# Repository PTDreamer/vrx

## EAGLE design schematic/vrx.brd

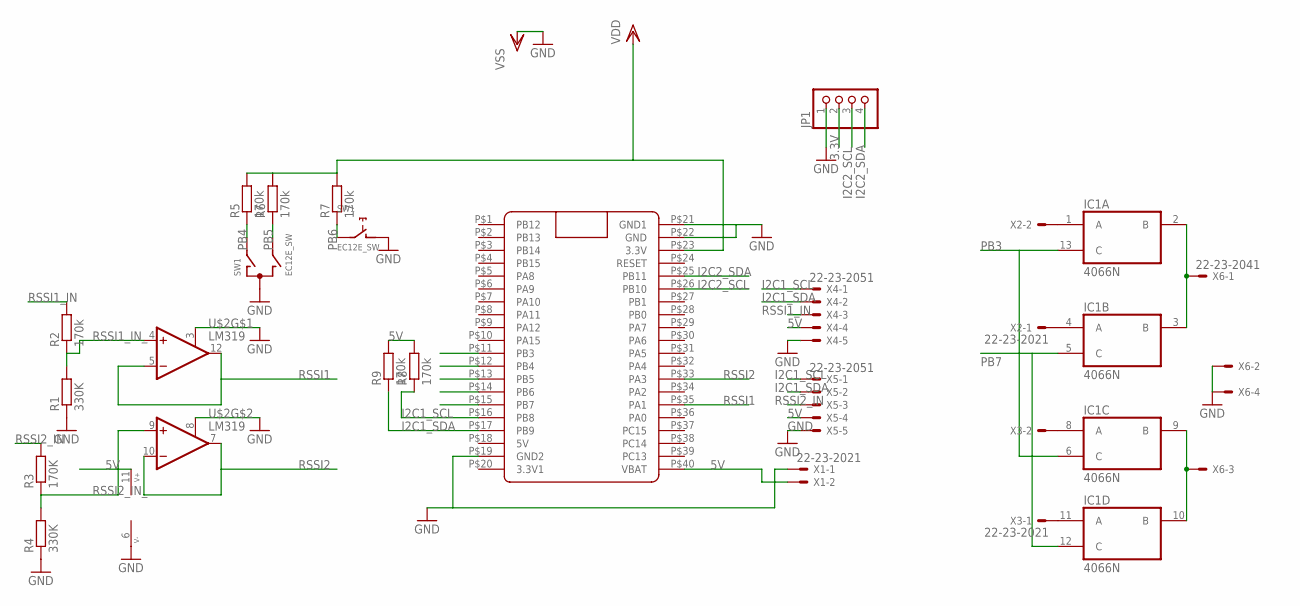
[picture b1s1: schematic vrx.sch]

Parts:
IC1: 4066N; DIL14
JP1: PINHD-1X4; 1X04
R1, R4: 330K; 0204/7
R2, R5, R6, R7, R8, R9: 170k; 0204/7
R3: 170K; 0204/7
SW1: EC12E_SW; ALPS_EC12E_SW
U$1: BLUE_PILLADVANCED; BLUE_PILL_ADV
U$2: LM319; DIL14
X1, X2, X3: 22-23-2021
X4, X5: 22-23-2051
X6: 22-23-2041

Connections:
3.3V: JP1.2
5V: R8.2, R9.2, U$1.P$40 (VBAT), U$2.11 (V+), X1.2, X4.4, X5.4
GND: IC1.7 (VSS), JP1.1, R1.1, R4.1, SW1.C, SW1.D (1), U$1.P$19 (GND2), U$1.P$21 (GND1), U$1.P$22 (GND), U$2.3 (SHDN), U$2.6 (V-), U$2.8 (SHDN), X1.1, X4.5, X5.5, X6.2, X6.4
I2C1_SCL: R8.1, U$1.P$16 (PB8), X4.1, X5.1
I2C1_SDA: R9.1, U$1.P$17 (PB9), X4.2, X5.2
I2C2_SCL: JP1.3, U$1.P$26 (PB10)
I2C2_SDA: JP1.4, U$1.P$25 (PB11)
unnamed: IC1.2 (B), IC1.3 (B), X6.1
unnamed: IC1.9 (B), IC1.10 (B), X6.3
unnamed: IC1.1 (A), X2.2
unnamed: IC1.4 (A), X2.1
unnamed: IC1.8 (A), X3.2
unnamed: IC1.11 (A), X3.1
PB3: IC1.6 (C), IC1.13 (C), U$1.P$11 (PB3)
PB4: R5.1, SW1.A, U$1.P$12 (PB4)
PB5: R6.1, SW1.B, U$1.P$13 (PB5)
PB6: R7.1, SW1.E (2), U$1.P$14 (PB6)
PB7: IC1.5 (C), IC1.12 (C), U$1.P$15 (PB7)
RSSI1: U$1.P$35 (PA1), U$2.5 (-IN), U$2.12 (OUT)
RSSI1_IN: R2.2, X4.3
RSSI1_IN_: R1.2, R2.1, U$2.4 (+IN)
RSSI2: U$1.P$33 (PA3), U$2.7 (OUT), U$2.10 (-IN)
RSSI2_IN: R3.2, X5.3
RSSI2_IN_: R3.1, R4.2, U$2.9 (+IN)
VDD: IC1.14 (VDD), R5.2, R6.2, R7.2, U$1.P$23 (3.3V)

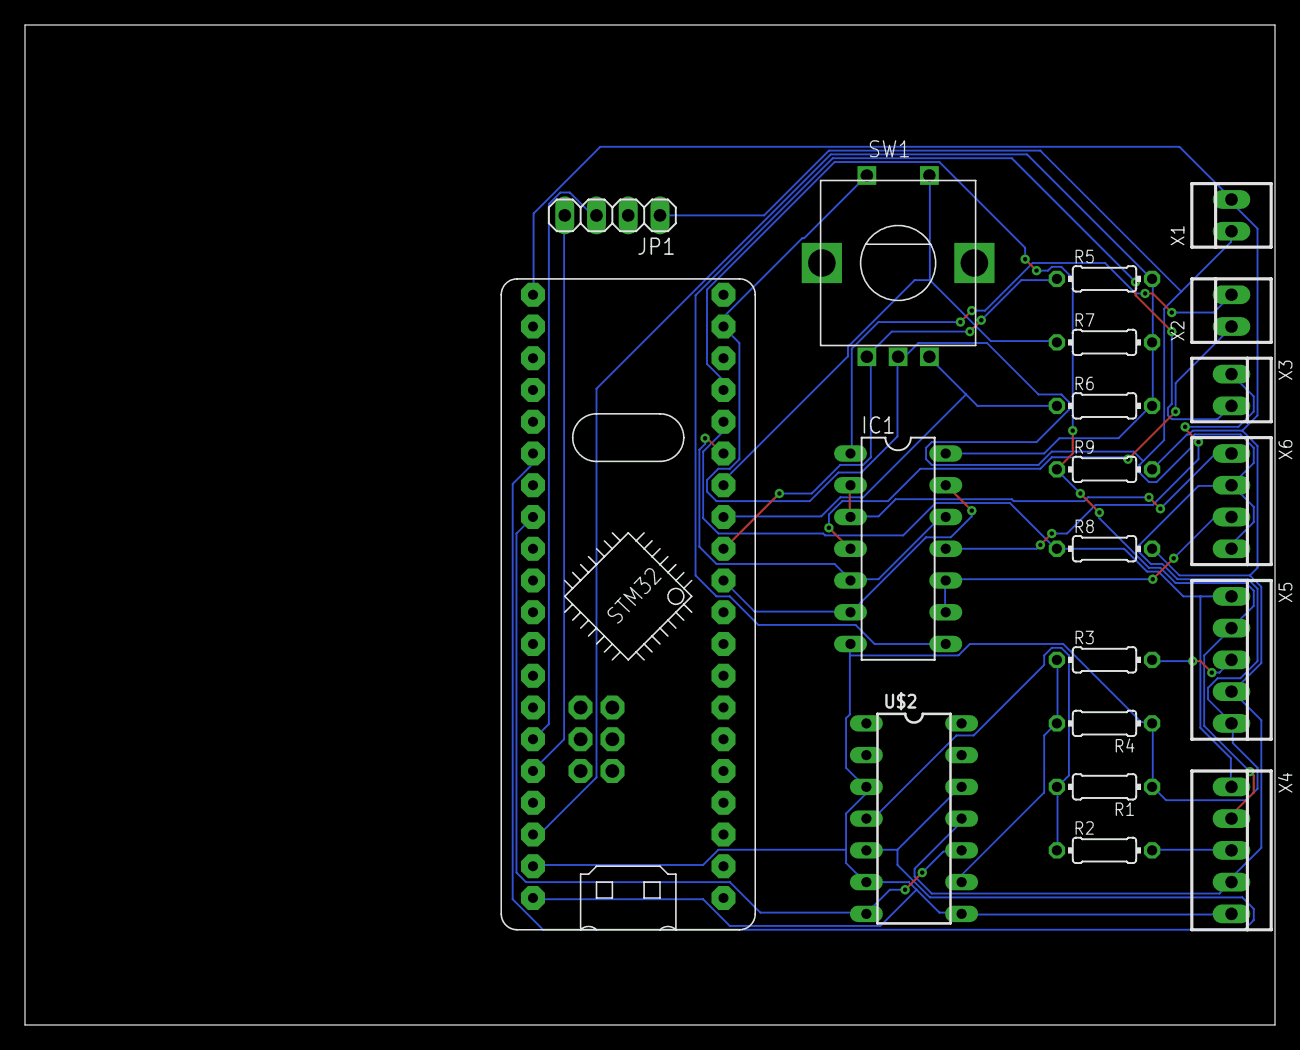
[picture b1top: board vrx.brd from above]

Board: 2 copper layers, 100.0 x 80.0 mm, 20 parts (0 on the bottom side), 24 nets.

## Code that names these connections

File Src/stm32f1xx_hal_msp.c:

/**
  ******************************************************************************
  * File Name          : stm32f1xx_hal_msp.c
  * Description        : This file provides code for the MSP Initialization 
  *                      and de-Initialization codes.
  ******************************************************************************
  ** This notice applies to any and all portions of this file
  * that are not between comment pairs USER CODE BEGIN and
  * USER CODE END. Other portions of this file, whether 
  * inserted by the user or by software development tools
  * are owned by their respective copyright owners.
  *
  * COPYRIGHT(c) 2017 STMicroelectronics
  *
  * Redistribution and use in source and binary forms, with or without modification,
  * are permitted provided that the following conditions are met:
  *   1. Redistributions of source code must retain the above copyright notice,
  *      this list of conditions and the following disclaimer.
  *   2. Redistributions in binary form must reproduce the above copyright notice,
  *      this list of conditions and the following disclaimer in the documentation
  *      and/or other materials provided with the distribution.
  *   3. Neither the name of STMicroelectronics nor the names of its contributors
  *      may be used to endorse or promote products derived from this software
  *      without specific prior written permission.
  *
  * THIS SOFTWARE IS PROVIDED BY THE COPYRIGHT HOLDERS AND CONTRIBUTORS "AS IS"
  * AND ANY EXPRESS OR IMPLIED WARRANTIES, INCLUDING, BUT NOT LIMITED TO, THE
  * IMPLIED WARRANTIES OF MERCHANTABILITY AND FITNESS FOR A PARTICULAR PURPOSE ARE
  * DISCLAIMED. IN NO EVENT SHALL THE COPYRIGHT HOLDER OR CONTRIBUTORS BE LIABLE
  * FOR ANY DIRECT, INDIRECT, INCIDENTAL, SPECIAL, EXEMPLARY, OR CONSEQUENTIAL
  * DAMAGES (INCLUDING, BUT NOT LIMITED TO, PROCUREMENT OF SUBSTITUTE GOODS OR
  * SERVICES; LOSS OF USE, DATA, OR PROFITS; OR BUSINESS INTERRUPTION) HOWEVER
  * CAUSED AND ON ANY THEORY OF LIABILITY, WHETHER IN CONTRACT, STRICT LIABILITY,
  * OR TORT (INCLUDING NEGLIGENCE OR OTHERWISE) ARISING IN ANY WAY OUT OF THE USE
  * OF THIS SOFTWARE, EVEN IF ADVISED OF THE POSSIBILITY OF SUCH DAMAGE.
  *
  ******************************************************************************
  */
/* Includes ------------------------------------------------------------------*/
#include "stm32f1xx_hal.h"

/* USER CODE BEGIN 0 */

/* USER CODE END 0 */
/**
  * Initializes the Global MSP.
  */
void HAL_MspInit(void)
{
  /* USER CODE BEGIN MspInit 0 */

  /* USER CODE END MspInit 0 */

  __HAL_RCC_AFIO_CLK_ENABLE();

  HAL_NVIC_SetPriorityGrouping(NVIC_PRIORITYGROUP_4);

  /* System interrupt init*/
  /* MemoryManagement_IRQn interrupt configuration */
  HAL_NVIC_SetPriority(MemoryManagement_IRQn, 0, 0);
  /* BusFault_IRQn interrupt configuration */
  HAL_NVIC_SetPriority(BusFault_IRQn, 0, 0);
  /* UsageFault_IRQn interrupt configuration */
  HAL_NVIC_SetPriority(UsageFault_IRQn, 0, 0);
  /* SVCall_IRQn interrupt configuration */
  HAL_NVIC_SetPriority(SVCall_IRQn, 0, 0);
  /* DebugMonitor_IRQn interrupt configuration */
  HAL_NVIC_SetPriority(DebugMonitor_IRQn, 0, 0);
  /* PendSV_IRQn interrupt configuration */
  HAL_NVIC_SetPriority(PendSV_IRQn, 0, 0);
  /* SysTick_IRQn interrupt configuration */
  HAL_NVIC_SetPriority(SysTick_IRQn, 0, 0);

    /**NOJTAG: JTAG-DP Disabled and SW-DP Enabled 
    */
  __HAL_AFIO_REMAP_SWJ_NOJTAG();

  /* USER CODE BEGIN MspInit 1 */

  /* USER CODE END MspInit 1 */
}

void HAL_ADC_MspInit(ADC_HandleTypeDef* hadc)
{

  GPIO_InitTypeDef GPIO_InitStruct;
  if(hadc->Instance==ADC1)
  {
  /* USER CODE BEGIN ADC1_MspInit 0 */

  /* USER CODE END ADC1_MspInit 0 */
    /* Peripheral clock enable */
    __HAL_RCC_ADC1_CLK_ENABLE();
  
    /**ADC1 GPIO Configuration    
    PA1     ------> ADC1_IN1
    */
    GPIO_InitStruct.Pin = GUN_TEMP_Pin;
    GPIO_InitStruct.Mode = GPIO_MODE_ANALOG;
    HAL_GPIO_Init(GUN_TEMP_GPIO_Port, &GPIO_InitStruct);

  /* USER CODE BEGIN ADC1_MspInit 1 */

  /* USER CODE END ADC1_MspInit 1 */
  }
  else if(hadc->Instance==ADC2)
  {
  /* USER CODE BEGIN ADC2_MspInit 0 */

  /* USER CODE END ADC2_MspInit 0 */
    /* Peripheral clock enable */
    __HAL_RCC_ADC2_CLK_ENABLE();

    /**ADC2 GPIO Configuration
    PA3     ------> ADC2_IN3
    */
    GPIO_InitStruct.Pin = GPIO_PIN_3;
    GPIO_InitStruct.Mode = GPIO_MODE_ANALOG;
    HAL_GPIO_Init(GPIOA, &GPIO_InitStruct);

  /* USER CODE BEGIN ADC2_MspInit 1 */

  /* USER CODE END ADC2_MspInit 1 */
  }

}

void HAL_ADC_MspDeInit(ADC_HandleTypeDef* hadc)
{

  if(hadc->Instance==ADC1)
  {
  /* USER CODE BEGIN ADC1_MspDeInit 0 */

  /* USER CODE END ADC1_MspDeInit 0 */
    /* Peripheral clock disable */
    __HAL_RCC_ADC1_CLK_DISABLE();
  
    /**ADC1 GPIO Configuration    
    PA1     ------> ADC1_IN1
    */
    HAL_GPIO_DeInit(GUN_TEMP_GPIO_Port, GUN_TEMP_Pin);

  /* USER CODE BEGIN ADC1_MspDeInit 1 */

  /* USER CODE END ADC1_MspDeInit 1 */
  }
  else if(hadc->Instance==ADC2)
  {
  /* USER CODE BEGIN ADC2_MspDeInit 0 */

  /* USER CODE END ADC2_MspDeInit 0 */
    /* Peripheral clock disable */
    __HAL_RCC_ADC2_CLK_DISABLE();

    /**ADC2 GPIO Configuration
    PA3     ------> ADC2_IN3
    */
    HAL_GPIO_DeInit(GPIOA, GPIO_PIN_3);

  /* USER CODE BEGIN ADC2_MspDeInit 1 */

  /* USER CODE END ADC2_MspDeInit 1 */
  }

}
void HAL_I2C_MspInit(I2C_HandleTypeDef* hi2c)
{

  GPIO_InitTypeDef GPIO_InitStruct;
  if(hi2c->Instance==I2C1)
  {
  /* USER CODE BEGIN I2C1_MspInit 0 */

  /* USER CODE END I2C1_MspInit 0 */

    /**I2C1 GPIO Configuration
    PB8     ------> I2C1_SCL
    PB9     ------> I2C1_SDA
    */
    GPIO_InitStruct.Pin = GPIO_PIN_8|GPIO_PIN_9;
    GPIO_InitStruct.Mode = GPIO_MODE_AF_OD;
    GPIO_InitStruct.Speed = GPIO_SPEED_FREQ_HIGH;
    HAL_GPIO_Init(GPIOB, &GPIO_InitStruct);

    __HAL_AFIO_REMAP_I2C1_ENABLE();

    /* Peripheral clock enable */
    __HAL_RCC_I2C1_CLK_ENABLE();
  /* USER CODE BEGIN I2C1_MspInit 1 */

  /* USER CODE END I2C1_MspInit 1 */
  }
  else if(hi2c->Instance==I2C2)
  {
  /* USER CODE BEGIN I2C2_MspInit 0 */

  /* USER CODE END I2C2_MspInit 0 */
  
    /**I2C2 GPIO Configuration
    PB10     ------> I2C2_SCL
    PB11     ------> I2C2_SDA
    */
    GPIO_InitStruct.Pin = GPIO_PIN_10|GPIO_PIN_11;
    GPIO_InitStruct.Mode = GPIO_MODE_AF_OD;
    GPIO_InitStruct.Speed = GPIO_SPEED_FREQ_HIGH;
    HAL_GPIO_Init(GPIOB, &GPIO_InitStruct);

    /* Peripheral clock enable */
    __HAL_RCC_I2C2_CLK_ENABLE();
  /* USER CODE BEGIN I2C2_MspInit 1 */

  /* USER CODE END I2C2_MspInit 1 */
  }

}

void HAL_I2C_MspDeInit(I2C_HandleTypeDef* hi2c)
{

  if(hi2c->Instance==I2C1)
  {
  /* USER CODE BEGIN I2C1_MspDeInit 0 */

  /* USER CODE END I2C1_MspDeInit 0 */
    /* Peripheral clock disable */
    __HAL_RCC_I2C1_CLK_DISABLE();

    /**I2C1 GPIO Configuration
    PB8     ------> I2C1_SCL
    PB9     ------> I2C1_SDA
    */
    HAL_GPIO_DeInit(GPIOB, GPIO_PIN_8|GPIO_PIN_9);

  /* USER CODE BEGIN I2C1_MspDeInit 1 */

  /* USER CODE END I2C1_MspDeInit 1 */
  }
  else if(hi2c->Instance==I2C2)
  {
  /* USER CODE BEGIN I2C2_MspDeInit 0 */

  /* USER CODE END I2C2_MspDeInit 0 */
    /* Peripheral clock disable */
    __HAL_RCC_I2C2_CLK_DISABLE();

    /**I2C2 GPIO Configuration
    PB10     ------> I2C2_SCL
    PB11     ------> I2C2_SDA
    */
    HAL_GPIO_DeInit(GPIOB, GPIO_PIN_10|GPIO_PIN_11);

  /* USER CODE BEGIN I2C2_MspDeInit 1 */

  /* USER CODE END I2C2_MspDeInit 1 */
  }

}


void HAL_UART_MspInit(UART_HandleTypeDef* huart)
{

  GPIO_InitTypeDef GPIO_InitStruct;
  if(huart->Instance==USART1)
  {
  /* USER CODE BEGIN USART1_MspInit 0 */

  /* USER CODE END USART1_MspInit 0 */
    /* Peripheral clock enable */
    __HAL_RCC_USART1_CLK_ENABLE();

    /**USART1 GPIO Configuration
    PA9     ------> USART1_TX
    PA10     ------> USART1_RX
    */
    GPIO_InitStruct.Pin = GPIO_PIN_9;
    GPIO_InitStruct.Mode = GPIO_MODE_AF_PP;
    GPIO_InitStruct.Speed = GPIO_SPEED_FREQ_HIGH;
    HAL_GPIO_Init(GPIOA, &GPIO_InitStruct);

    GPIO_InitStruct.Pin = GPIO_PIN_10;
    GPIO_InitStruct.Mode = GPIO_MODE_INPUT;
    GPIO_InitStruct.Pull = GPIO_NOPULL;
    HAL_GPIO_Init(GPIOA, &GPIO_InitStruct);

  /* USER CODE BEGIN USART1_MspInit 1 */

  /* USER CODE END USART1_MspInit 1 */
  }

}

void HAL_UART_MspDeInit(UART_HandleTypeDef* huart)
{

  if(huart->Instance==USART1)
  {
  /* USER CODE BEGIN USART1_MspDeInit 0 */

  /* USER CODE END USART1_MspDeInit 0 */
    /* Peripheral clock disable */
    __HAL_RCC_USART1_CLK_DISABLE();

    /**USART1 GPIO Configuration
    PA9     ------> USART1_TX
    PA10     ------> USART1_RX
    */
    HAL_GPIO_DeInit(GPIOA, GPIO_PIN_9|GPIO_PIN_10);

  /* USER CODE BEGIN USART1_MspDeInit 1 */

  /* USER CODE END USART1_MspDeInit 1 */
  }

}

/* USER CODE BEGIN 1 */

/* USER CODE END 1 */

/**
  * @}
  */

/**
  * @}
  */

/************************ (C) COPYRIGHT STMicroelectronics *****END OF FILE****/

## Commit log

2018-02-08 working
2018-02-08 clean garbage
2018-02-08 more cleaning

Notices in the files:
parts and their libraries:
op-amp: Copyright (C) 2006 by Bob Starr
